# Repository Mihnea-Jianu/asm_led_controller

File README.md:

# ASM LED Controller

The ASM LED Controller Board is an algorithmic state machine, designed to store
and run a microprogram which controls the states of the 22 LEDs that make up the
on-board, heart-shaped LED array.

## Features

- 22 individually addressable LEDs.
- Microprograms up to 1023 microinstructions long.
- 3 separate clock speeds.
- Fully digital flash interface.

## Schematic Overview

### Clock Generator

The clock generator is simply a `CD4060BE binary counter`, which is setup to use
its built-in oscillator with the RC setup.

From the frequencies generated at the pins of the chip, I have selected a 
slow one `[Q8]` and a fast one `[Q7]`, and hooked them up to a SP3T slide
switch, for clock speed selection. The third pole of the slide switch is 
connected to GND, equivalent to a paused clock.

The output of this slide switch is the main clock of the circuit.

### Progam Counter

The program counter is another `CD4060BE binary counter`, whose outputs are used
to iterate through the addresses of the memory chips.

**When in RUN mode** 
- The counter is driven up by the pulse of the clock generator.
- The counter is reset when the current instruction's reset bit is pulled high.

**When in FLASH mode**
- The counter is driven up by the flash interface's XCLK.
- The counter is reset by the flash interface's XRST.

### Microprogram Memory

The microprogram memroy consists of 3 concatenated `AS6C1008-55PCN SRAM` chips.
Their addresses are 8 bits wide, so we have a total of 24 bits per address.

The current address of the memory chips is controlled by the program counter,
and the outputs of the memory chips go directly to the LED array.

**When in RUN mode**
- We read the LED configuration stored in memory, at the current address.
- We read the reset bit stored in memory, at the current address.

**When in FLASH mode**
- We write an LED configuration to the memory, at the current address.
- We write the reset bit to the memory, at the current address.

## Flashing

To flash the device, you will need a development board that has 26 usable digital
output pins, like the **Arduino Mega**.

The `asm_led_flasher.ino` sketch, under `software/`, is setup to use pins 22-47
of the Arduino Mega, which must be connected to the flash interface.

**The flash interface consists of 26 digital pins:**

<table>
    <thead> 
        <tr>
            <th>Pin</th> <th>Arduino Mega Pin</th> <th>Type</th> <th>Role</th>
        </tr> 
    </thead>
    <tbody>
        <tr>
            <td>L1 - L22</td>
            <td>26 - 47</td>
            <td>data pin</td>
            <td>load LED configurations into memory</td>
        </tr>
        <tr>
            <td>RST</td>
            <td>25</td>
            <td>data pin</td>
            <td>load reset bit into memory</td>
        </tr>
        <tr>
            <td>XWE</td>
            <td>24</td>
            <td>control pin</td>
            <td>write the values at the data pins into memory</td>
        </tr>
        <tr>
            <td>XRST</td>
            <td>23</td>
            <td>control pin</td>
            <td>reset the current address of the memory</td>
        </tr>
        <tr>
            <td>XCLK</td>
            <td>22</td>
            <td>control pin</td>
            <td>increment the current address of the memory</td>
        </tr>
    </tbody>
</table>

**Set the on-board switches to the following configuration:**

<table>
    <thead> 
        <tr>
            <th>Switch</th> <th>Position</th>
        </tr> 
    </thead>
    <tbody>
        <tr>
            <td>ON/OFF</td>
            <td>ON</td>
        </tr>
        <tr>
            <td>ON/OFF LED</td>
            <td>ON</td>
        </tr>
        <tr>
            <td>RUN/FLASH</td>
            <td>FLASH</td>
        </tr>
        <tr>
            <td>FREQUENCY</td>
            <td>PAUSE</td>
        </tr>
    </tbody>
</table>

Once everything is setup, connect the Arduino Mega to your computer, and upload
the `software/asm_led_flasher.ino` sketch to it.

- When the builtin LED lights up, you have 10 seconds to flip the top RUN/FLASH
switch back to RUN. 

- When the builtin LED lights up again, you can flip the bottom RUN/FLASH switch
back to RUN, disconnect the flash interface from the Arduino Mega, and unpause
the clock.

## Repository Contents

`hardware/`
- KiCad project files (schematic, layout).
- Custom libraries (symbols, footprints, 3D models, library tables).

`software/`
- Arduino IDE sketch, for flashing the board.

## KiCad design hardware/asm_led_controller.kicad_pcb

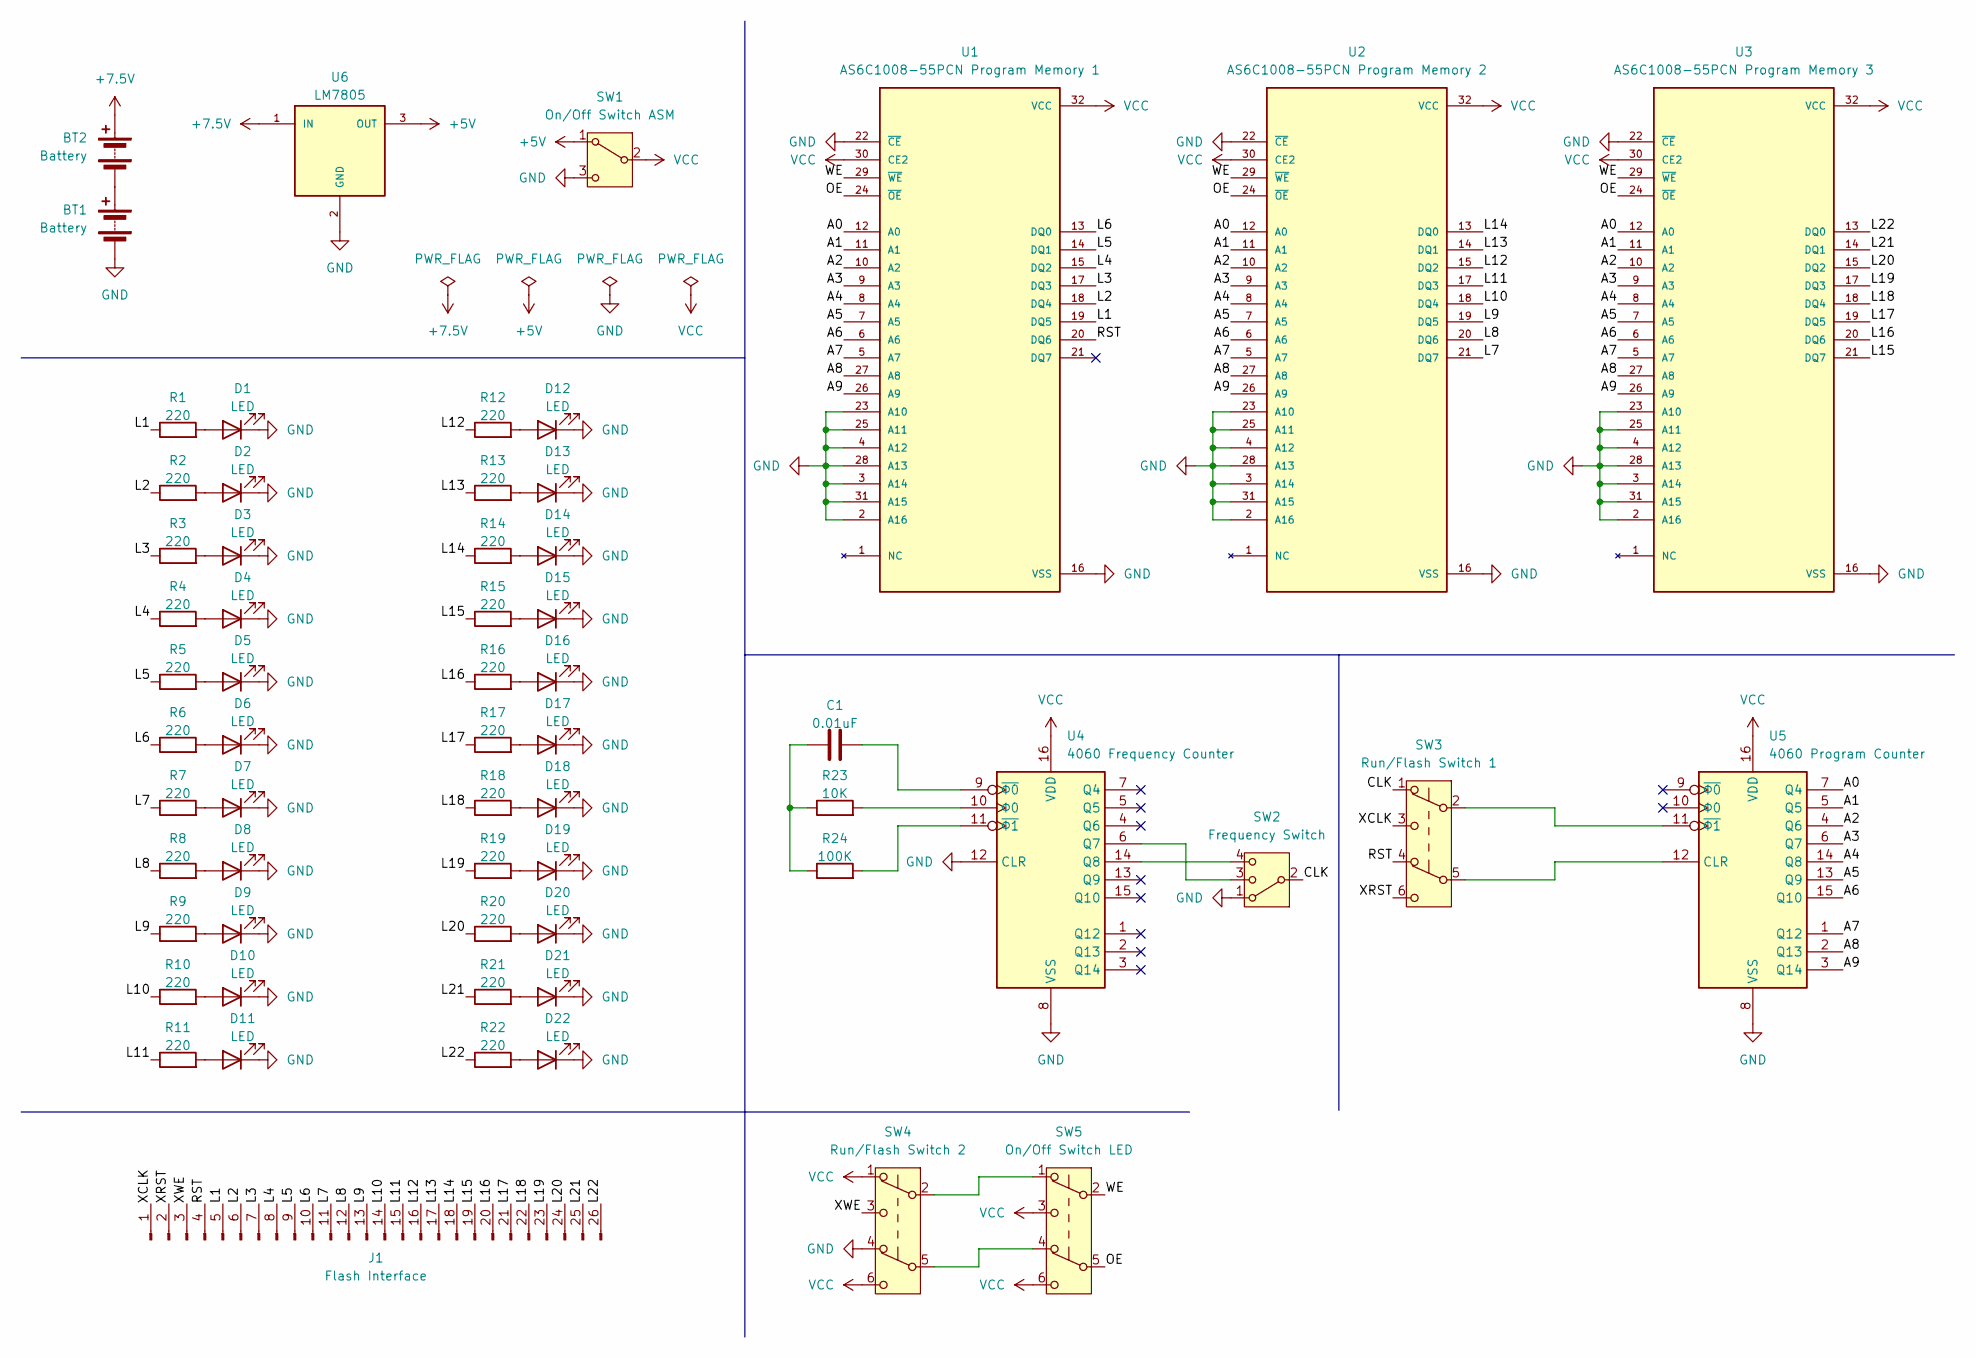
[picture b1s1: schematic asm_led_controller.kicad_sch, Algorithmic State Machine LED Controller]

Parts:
BT1, BT2: Battery; BAT_BH-18650-PC
C1: 0.01uF; C_Disc_D3.8mm_W2.6mm_P2.50mm
D1, D2, D3, D4, D5, D6, D7, D8, D9, D10, D11, D12, D13, D14, D15, D16, D17, D18, D19, D20, D21, D22: LED; LED_D5.0mm
J1: Flash Interface; PinHeader_2x13_P2.54mm_Vertical
R1, R2, R3, R4, R5, R6, R7, R8, R9, R10, R11, R12, R13, R14, R15, R16, R17, R18, R19, R20, R21, R22: 220; R_Axial_DIN0207_L6.3mm_D2.5mm_P7.62mm_Horizontal
R23: 10K; R_Axial_DIN0207_L6.3mm_D2.5mm_P7.62mm_Horizontal
R24: 100K; R_Axial_DIN0207_L6.3mm_D2.5mm_P7.62mm_Horizontal
SW1: On/Off Switch ASM; SW_Slide_SPDT_Straight_CK_OS102011MS2Q
SW2: Frequency Switch; OS102011MS8QP1
SW3: Run/Flash Switch 1; JS202011CQN
SW4: Run/Flash Switch 2; JS202011CQN
SW5: On/Off Switch LED; JS202011CQN
U1: AS6C1008-55PCN Program Memory 1; DIP1524W45P254L4191H419Q32
U2: AS6C1008-55PCN Program Memory 2; DIP1524W45P254L4191H419Q32
U3: AS6C1008-55PCN Program Memory 3; DIP1524W45P254L4191H419Q32
U4: 4060 Frequency Counter; DIP794W45P254L1969H508Q16
U5: 4060 Program Counter; DIP794W45P254L1969H508Q16
U6: LM7805; TO220

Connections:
+5V: SW1.1 (A), U6.3 (OUT); also elsewhere on the board
+7.5V: BT2.1 (+), U6.1 (IN)
/A0: U1.12 (A0), U2.12 (A0), U3.12 (A0), U5.7 (Q4)
/A1: U1.11 (A1), U2.11 (A1), U3.11 (A1), U5.5 (Q5)
/A2: U1.10 (A2), U2.10 (A2), U3.10 (A2), U5.4 (Q6)
/A3: U1.9 (A3), U2.9 (A3), U3.9 (A3), U5.6 (Q7)
/A4: U1.8 (A4), U2.8 (A4), U3.8 (A4), U5.14 (Q8)
/A5: U1.7 (A5), U2.7 (A5), U3.7 (A5), U5.13 (Q9)
/A6: U1.6 (A6), U2.6 (A6), U3.6 (A6), U5.15 (Q10)
/A7: U1.5 (A7), U2.5 (A7), U3.5 (A7), U5.1 (Q12)
/A8: U1.27 (A8), U2.27 (A8), U3.27 (A8), U5.2 (Q13)
/A9: U1.26 (A9), U2.26 (A9), U3.26 (A9), U5.3 (Q14)
/CLK: SW2.2, SW3.1 (A); also elsewhere on the board
/L1: J1.5, R1.1, U1.19 (DQ5); also elsewhere on the board
/L2: J1.6, R2.1, U1.18 (DQ4); also elsewhere on the board
/L3: J1.7, R3.1, U1.17 (DQ3); also elsewhere on the board
/L4: J1.8, R4.1, U1.15 (DQ2); also elsewhere on the board
/L5: J1.9, R5.1, U1.14 (DQ1); also elsewhere on the board
/L6: J1.10, R6.1, U1.13 (DQ0); also elsewhere on the board
/L7: J1.11, R7.1, U2.21 (DQ7); also elsewhere on the board
/L8: J1.12, R8.1, U2.20 (DQ6); also elsewhere on the board
/L9: J1.13, R9.1, U2.19 (DQ5); also elsewhere on the board
/L10: J1.14, R10.1, U2.18 (DQ4); also elsewhere on the board
/L11: J1.15, R11.1, U2.17 (DQ3); also elsewhere on the board
/L12: J1.16, R12.1, U2.15 (DQ2); also elsewhere on the board
/L13: J1.17, R13.1, U2.14 (DQ1); also elsewhere on the board
/L14: J1.18, R14.1, U2.13 (DQ0); also elsewhere on the board
/L15: J1.19, R15.1, U3.21 (DQ7); also elsewhere on the board
/L16: J1.20, R16.1, U3.20 (DQ6); also elsewhere on the board
/L17: J1.21, R17.1, U3.19 (DQ5); also elsewhere on the board
/L18: J1.22, R18.1, U3.18 (DQ4); also elsewhere on the board
/L19: J1.23, R19.1, U3.17 (DQ3); also elsewhere on the board
/L20: J1.24, R20.1, U3.15 (DQ2); also elsewhere on the board
/L21: J1.25, R21.1, U3.14 (DQ1); also elsewhere on the board
/L22: J1.26, R22.1, U3.13 (DQ0); also elsewhere on the board
/OE: SW5.5 (B), U1.24 (~OE), U2.24 (~OE), U3.24 (~OE); also elsewhere on the board
/RST: J1.4, SW3.4 (A), U1.20 (DQ6); also elsewhere on the board
/WE: SW5.2 (B), U1.29 (~WE), U2.29 (~WE), U3.29 (~WE); also elsewhere on the board
/XCLK: J1.1, SW3.3 (C); also elsewhere on the board
/XRST: J1.2, SW3.6 (C); also elsewhere on the board
GND: BT1.2 (-), D1.1 (K), D2.1 (K), D3.1 (K), D4.1 (K), D5.1 (K), D6.1 (K), D7.1 (K), D8.1 (K), D9.1 (K), D10.1 (K), D11.1 (K), D12.1 (K), D13.1 (K), D14.1 (K), D15.1 (K), D16.1 (K), D17.1 (K), D18.1 (K), D19.1 (K), D20.1 (K), D21.1 (K), D22.1 (K), SW1.3 (C), SW2.1, SW4.4 (A), U1.2 (A16), U1.3 (A14), U1.4 (A12), U1.16 (VSS), U1.22 (~CE), U1.23 (A10), U1.25 (A11), U1.28 (A13), U1.31 (A15), U2.2 (A16), U2.3 (A14), U2.4 (A12), U2.16 (VSS), U2.22 (~CE), U2.23 (A10), U2.25 (A11), U2.28 (A13), U2.31 (A15), U3.2 (A16), U3.3 (A14), U3.4 (A12), U3.16 (VSS), U3.22 (~CE), U3.23 (A10), U3.25 (A11), U3.28 (A13), U3.31 (A15), U4.8 (VSS), U4.12 (CLR), U5.8 (VSS), U6.2 (GND); also elsewhere on the board
unnamed: BT1.1 (+), BT2.2 (-)
unnamed: C1.2, R23.1, R24.1
unnamed: D1.2 (A), R1.2
unnamed: D2.2 (A), R2.2
unnamed: D3.2 (A), R3.2
unnamed: D4.2 (A), R4.2
unnamed: D5.2 (A), R5.2
unnamed: D6.2 (A), R6.2
unnamed: D7.2 (A), R7.2
unnamed: D8.2 (A), R8.2
unnamed: D9.2 (A), R9.2
unnamed: D10.2 (A), R10.2
unnamed: D11.2 (A), R11.2
unnamed: D12.2 (A), R12.2
unnamed: D13.2 (A), R13.2
unnamed: D14.2 (A), R14.2
unnamed: D15.2 (A), R15.2
unnamed: D16.2 (A), R16.2
unnamed: D17.2 (A), R17.2
unnamed: D18.2 (A), R18.2
unnamed: D19.2 (A), R19.2
unnamed: D20.2 (A), R20.2
unnamed: D21.2 (A), R21.2
unnamed: D22.2 (A), R22.2
unnamed: J1.3, SW4.3 (C)
unnamed: SW4.2 (B), SW5.1 (A)
unnamed: SW4.5 (B), SW5.4 (A)
unnamed 71: SW2.3, U4.6 (Q7); also elsewhere on the board
unnamed 72: SW2.4, U4.14 (Q8); also elsewhere on the board
unnamed: C1.1, U4.9 (~Φ0)
unnamed: R24.2, U4.11 (~Φ1)
unnamed: R23.2, U4.10 (Φ0)
unnamed: SW3.5 (B), U5.12 (CLR)
unnamed: SW3.2 (B), U5.11 (~Φ1)
VCC: SW1.2 (B), SW4.1 (A), SW4.6 (C), SW5.3 (C), SW5.6 (C), U1.30 (CE2), U1.32 (VCC), U2.30 (CE2), U2.32 (VCC), U3.30 (CE2), U3.32 (VCC), U4.16 (VDD), U5.16 (VDD); also elsewhere on the board

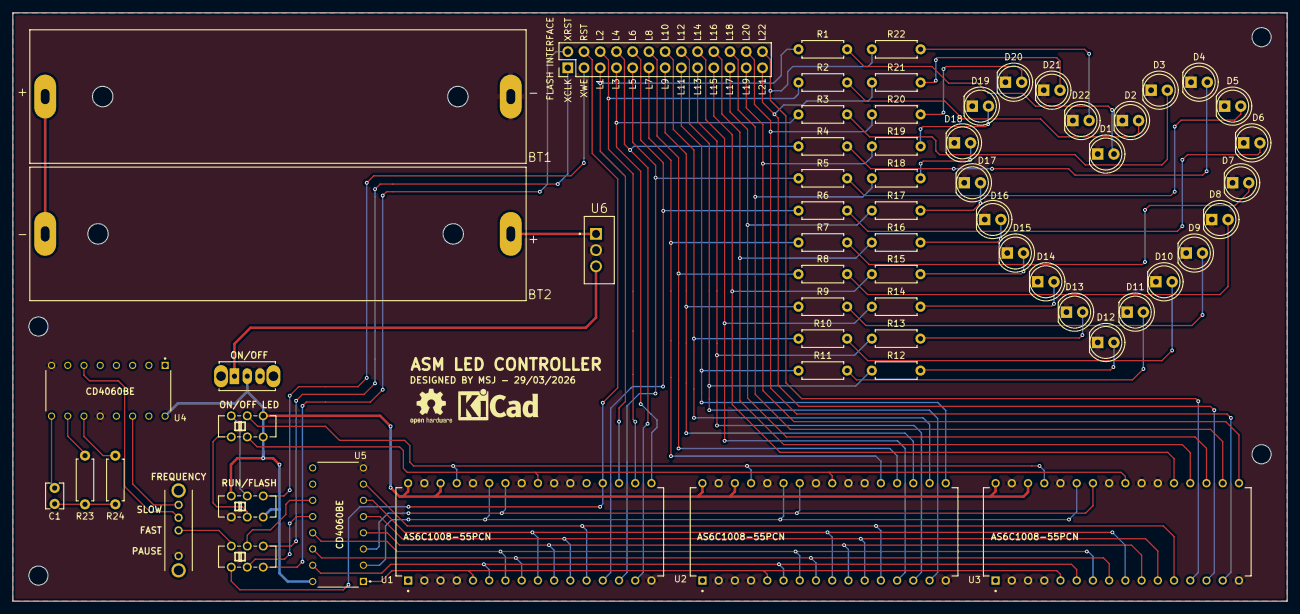
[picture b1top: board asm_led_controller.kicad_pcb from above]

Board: 2 copper layers, 199.5 x 92.1 mm, 61 parts (0 on the bottom side), 76 nets.

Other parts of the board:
FLASH INTERFACE: Flash Interface; PinHeader_2x13_P2.54mm_Vertical
FREQUENCY: Frequency Switch; OS102011MS8QP1
ON/OFF: On/Off Switch ASM; SW_Slide_SPDT_Straight_CK_OS102011MS2Q
ON/OFF LED: On/Off Switch LED; JS202011CQN
RUN/FLASH: Run/Flash Switch 2; JS202011CQN

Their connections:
+5V: ON/OFF.1 (A); also elsewhere on the board
/CLK: FREQUENCY.2; also elsewhere on the board
/L1: FLASH INTERFACE.5; also elsewhere on the board
/L2: FLASH INTERFACE.6; also elsewhere on the board
/L3: FLASH INTERFACE.7; also elsewhere on the board
/L4: FLASH INTERFACE.8; also elsewhere on the board
/L5: FLASH INTERFACE.9; also elsewhere on the board
/L6: FLASH INTERFACE.10; also elsewhere on the board
/L7: FLASH INTERFACE.11; also elsewhere on the board
/L8: FLASH INTERFACE.12; also elsewhere on the board
/L9: FLASH INTERFACE.13; also elsewhere on the board
/L10: FLASH INTERFACE.14; also elsewhere on the board
/L11: FLASH INTERFACE.15; also elsewhere on the board
/L12: FLASH INTERFACE.16; also elsewhere on the board
/L13: FLASH INTERFACE.17; also elsewhere on the board
/L14: FLASH INTERFACE.18; also elsewhere on the board
/L15: FLASH INTERFACE.19; also elsewhere on the board
/L16: FLASH INTERFACE.20; also elsewhere on the board
/L17: FLASH INTERFACE.21; also elsewhere on the board
/L18: FLASH INTERFACE.22; also elsewhere on the board
/L19: FLASH INTERFACE.23; also elsewhere on the board
/L20: FLASH INTERFACE.24; also elsewhere on the board
/L21: FLASH INTERFACE.25; also elsewhere on the board
/L22: FLASH INTERFACE.26; also elsewhere on the board
/OE: ON/OFF LED.5 (B); also elsewhere on the board
/RST: FLASH INTERFACE.4; also elsewhere on the board
/WE: ON/OFF LED.2 (B); also elsewhere on the board
/XCLK: FLASH INTERFACE.1; also elsewhere on the board
/XRST: FLASH INTERFACE.2; also elsewhere on the board
/XWE: FLASH INTERFACE.3, RUN/FLASH.3 (C)
GND: FREQUENCY.1, ON/OFF.3 (C), RUN/FLASH.4 (A); also elsewhere on the board
unnamed: ON/OFF LED.1 (A), RUN/FLASH.2 (B)
unnamed: ON/OFF LED.4 (A), RUN/FLASH.5 (B)
unnamed 71: FREQUENCY.3; also elsewhere on the board
unnamed 72: FREQUENCY.4; also elsewhere on the board
VCC: ON/OFF.2 (B), ON/OFF LED.3 (C), ON/OFF LED.6 (C), RUN/FLASH.1 (A), RUN/FLASH.6 (C); also elsewhere on the board

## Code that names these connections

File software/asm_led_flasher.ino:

// Each row is an instruction containing an LED configuration and the reset bit.
const unsigned char source[] = {
//  L1  L2  L3  L4  L5  L6  L7  L8  L9  L10 L11 L12 L13 L14 L15 L16 L17 L18 L19 L20 L21 L22 RST 
    1,  1,  1,  1,  0,  0,  0,  0,  0,  0,  0,  0,  0,  0,  0,  0,  0,  0,  0,  1,  1,  1,  0,
    1,  1,  1,  1,  1,  0,  0,  0,  0,  0,  0,  0,  0,  0,  0,  0,  0,  0,  0,  0,  1,  1,  0,
    1,  1,  1,  1,  1,  1,  0,  0,  0,  0,  0,  0,  0,  0,  0,  0,  0,  0,  0,  0,  0,  1,  0,
    1,  1,  1,  1,  1,  1,  1,  0,  0,  0,  0,  0,  0,  0,  0,  0,  0,  0,  0,  0,  0,  0,  0,
    0,  1,  1,  1,  1,  1,  1,  1,  0,  0,  0,  0,  0,  0,  0,  0,  0,  0,  0,  0,  0,  0,  0,
    0,  0,  1,  1,  1,  1,  1,  1,  1,  0,  0,  0,  0,  0,  0,  0,  0,  0,  0,  0,  0,  0,  0,
    0,  0,  0,  1,  1,  1,  1,  1,  1,  1,  0,  0,  0,  0,  0,  0,  0,  0,  0,  0,  0,  0,  0,
    0,  0,  0,  0,  1,  1,  1,  1,  1,  1,  1,  0,  0,  0,  0,  0,  0,  0,  0,  0,  0,  0,  0,
    0,  0,  0,  0,  0,  1,  1,  1,  1,  1,  1,  1,  0,  0,  0,  0,  0,  0,  0,  0,  0,  0,  0,
    0,  0,  0,  0,  0,  0,  1,  1,  1,  1,  1,  1,  1,  0,  0,  0,  0,  0,  0,  0,  0,  0,  0,
    0,  0,  0,  0,  0,  0,  0,  1,  1,  1,  1,  1,  1,  1,  0,  0,  0,  0,  0,  0,  0,  0,  0,
    0,  0,  0,  0,  0,  0,  0,  0,  1,  1,  1,  1,  1,  1,  1,  0,  0,  0,  0,  0,  0,  0,  0,
    0,  0,  0,  0,  0,  0,  0,  0,  0,  1,  1,  1,  1,  1,  1,  1,  0,  0,  0,  0,  0,  0,  0,
    0,  0,  0,  0,  0,  0,  0,  0,  0,  0,  1,  1,  1,  1,  1,  1,  1,  0,  0,  0,  0,  0,  0,
    0,  0,  0,  0,  0,  0,  0,  0,  0,  0,  0,  1,  1,  1,  1,  1,  1,  1,  0,  0,  0,  0,  0,
    0,  0,  0,  0,  0,  0,  0,  0,  0,  0,  0,  0,  1,  1,  1,  1,  1,  1,  1,  0,  0,  0,  0,
    0,  0,  0,  0,  0,  0,  0,  0,  0,  0,  0,  0,  0,  1,  1,  1,  1,  1,  1,  1,  0,  0,  0,
    0,  0,  0,  0,  0,  0,  0,  0,  0,  0,  0,  0,  0,  0,  1,  1,  1,  1,  1,  1,  1,  0,  0,
    0,  0,  0,  0,  0,  0,  0,  0,  0,  0,  0,  0,  0,  0,  0,  1,  1,  1,  1,  1,  1,  1,  0,
    1,  0,  0,  0,  0,  0,  0,  0,  0,  0,  0,  0,  0,  0,  0,  0,  1,  1,  1,  1,  1,  1,  0,
    1,  1,  0,  0,  0,  0,  0,  0,  0,  0,  0,  0,  0,  0,  0,  0,  0,  1,  1,  1,  1,  1,  0,
    1,  1,  1,  0,  0,  0,  0,  0,  0,  0,  0,  0,  0,  0,  0,  0,  0,  0,  1,  1,  1,  1,  0,
    1,  1,  1,  1,  1,  1,  1,  1,  1,  1,  1,  1,  1,  1,  1,  1,  1,  1,  1,  1,  1,  1,  1  // Reset instruction, do not remove.
};

const unsigned char instructionSize = 23;

// Pin mapping.
const unsigned char led[22] = {26, 27, 28, 29, 30, 31, 32, 33, 34, 35, 36, 37, 38, 39, 40, 41, 42, 43, 44, 45, 46, 47};
const unsigned char xclk = 22;
const unsigned char xrst = 23;
const unsigned char xwe  = 24;
const unsigned char rst  = 25;

void flash() {
  // Reset the program counter.
  digitalWrite(xrst, HIGH);
  delay(100);
  digitalWrite(xrst, LOW);
  delay(100);

  // Iterate through instructions and write them.
  for(int i = 0; i < sizeof(source); i += instructionSize) {
    // Load the LED configuration from the current instruction.
    for(int j = 0; j < sizeof(led); j++) {
      digitalWrite(led[j], source[i + j]);
    }

    // Load the reset bit from the current instruction.
    digitalWrite(rst, source[i + instructionSize - 1]);

    // Let the data stabilise.
    delay(100);

    // Write the data.
    digitalWrite(xwe, LOW);
    delay(100);
    digitalWrite(xwe, HIGH);
    delay(100);

    // Advance to the next memory address.
    for(int j = 0; j < 8; j++) { // Must be done 8 times becuase the program counter advances on the 8th pulse of the clock.
      digitalWrite(xclk, HIGH);
      delay(100);
      digitalWrite(xclk, LOW);
      delay(100);
    }
  }

  // Turn on the builtin LED to signal that user has 10 seconds to flip the top RUN/FLASH switch back to RUN.
  digitalWrite(LED_BUILTIN, HIGH);
  delay(10000);
  digitalWrite(LED_BUILTIN, LOW);

  // Reset program counter.
  digitalWrite(xrst, HIGH);
  delay(100);
  digitalWrite(xrst, LOW);
  delay(100);

  // Turn on built-in LED to signal that the user can flip the bottom RUN/FLASH switch back to RUN,
  // as well as disconnect the flash interface and unpause the clock.
  digitalWrite(LED_BUILTIN, HIGH);
}

void setup() {
  // Set all pins to output mode and give them an initial state.
  for(int i = 0; i < sizeof(led); i++) {
    pinMode(led[i], OUTPUT);
    digitalWrite(led[i], LOW);
  }

  pinMode(LED_BUILTIN, OUTPUT);
  pinMode(rst,         OUTPUT);
  pinMode(xrst,        OUTPUT);
  pinMode(xclk,        OUTPUT);
  pinMode(xwe,         OUTPUT);

  digitalWrite(LED_BUILTIN, LOW);
  digitalWrite(rst,         LOW);
  digitalWrite(xrst,        LOW);
  digitalWrite(xclk,        LOW);
  digitalWrite(xwe,         HIGH);

  // Let the outputs stabilise and run the flash function.
  delay(100);
  flash();
}

void loop() {

}
